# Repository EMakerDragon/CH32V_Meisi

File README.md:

# CH32V_Meisi
これはUIAPduino Pro Micro CH32V003 V1.4をベースに5X7ドットマトリクスLEDを追加した基板名刺です。  
基本的にはUIAPduino Pro Micro CH32V003 V1.4と同じ設計なので同じように使用できます。

Test_program.inoはデフォルトで書き込んでいるプログラムです。  
全点灯,H,E,L,L,O,ランダム点灯 がボタンを押すごとに切り替わります。  
かなり汚いプログラムなので参考にはしないでください。

ベースにしたボード  
UIAPduino Pro Micro CH32V003 V1.4 https://www.uiap.jp/uiapduino/pro-micro/ch32v003/v1dot4

## License
This project is licensed under the Creative Commons Attribution-ShareAlike 4.0 International License.
- [View License Summary](https://creativecommons.org/licenses/by-sa/4.0/deed.ja)
- [View Full Legal Code](https://creativecommons.org/licenses/by-sa/4.0/legalcode)

このプロジェクトは、[YuukiUmeta-UIAP]による「UIAPduino Pro Micro CH32V003 V1.4」をベースにしており、
クリエイティブ・コモンズ 表示 - 継承 4.0 国際 ライセンスの下で提供されています。

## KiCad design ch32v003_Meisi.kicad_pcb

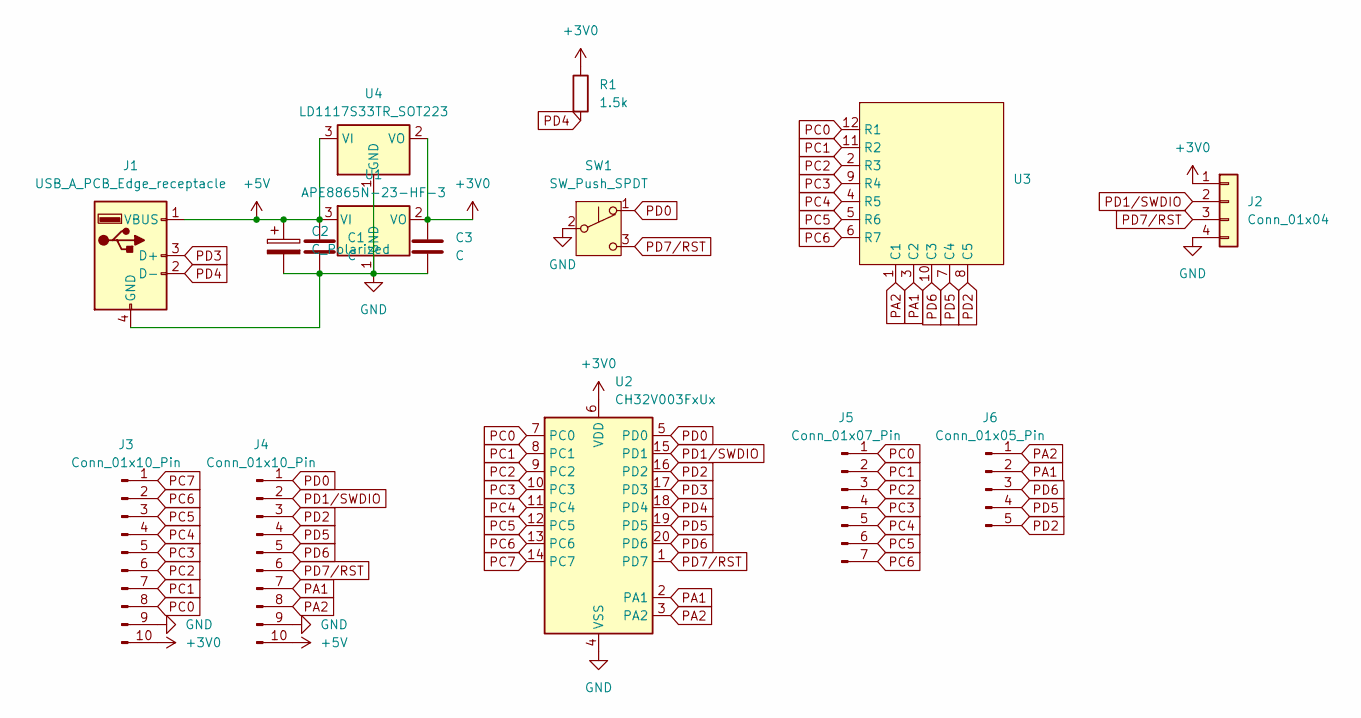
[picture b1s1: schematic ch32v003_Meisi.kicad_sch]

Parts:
C1, C3: C; C_0603_1608Metric
C2: C_Polarized; CP_Radial_D5.0mm_P2.50mm
J1: USB_A_PCB_Edge_receptacle
J2: Conn_01x04; DEBUG_ch32
J3, J4: Conn_01x10_Pin; PinHeader_1x10_P2.54mm_Vertical
J5: Conn_01x07_Pin; PinHeader_1x07_P2.54mm_Vertical
J6: Conn_01x05_Pin; PinHeader_1x05_P2.54mm_Vertical
R1: 1.5k
SW1: SW_Push_SPDT; Push_SW_2Level
U1: APE8865N-23-HF-3; SOT-23
U2: CH32V003FxUx; QFN-20-1EP_3x3mm_P0.4mm_EP1.65x1.65mm
U3: LED_MATRIX
U4: LD1117S33TR_SOT223; SOT-223-3_TabPin2

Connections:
+3V0: C3.1, J2.1, J3.10, R1.1, U1.2 (VO), U2.6 (VDD), U4.2 (VO)
+5V: C1.1, C2.1, J1.1 (VBUS), J4.10, U1.3 (VI), U4.3 (VI)
GND: C1.2, C2.2, C3.2, J1.4 (GND), J2.4, J3.9, J4.9, SW1.2 (B), U1.1 (GND), U2.4 (VSS), U2.21 (VSS), U4.1 (GND)
PA1: J4.7, J6.2, U2.2 (PA1), U3.3 (C2)
PA2: J4.8, J6.1, U2.3 (PA2), U3.1 (C1)
PC0: J3.8, J5.1, U2.7 (PC0), U3.12 (R1)
PC1: J3.7, J5.2, U2.8 (PC1), U3.11 (R2)
PC2: J3.6, J5.3, U2.9 (PC2), U3.2 (R3)
PC3: J3.5, J5.4, U2.10 (PC3), U3.9 (R4)
PC4: J3.4, J5.5, U2.11 (PC4), U3.4 (R5)
PC5: J3.3, J5.6, U2.12 (PC5), U3.5 (R6)
PC6: J3.2, J5.7, U2.13 (PC6), U3.6 (R7)
PC7: J3.1, U2.14 (PC7)
PD0: J4.1, SW1.1 (A), U2.5 (PD0)
PD1/SWDIO: J2.2, J4.2, U2.15 (PD1)
PD2: J4.3, J6.5, U2.16 (PD2), U3.8 (C5)
PD3: J1.3 (D+), U2.17 (PD3)
PD4: J1.2 (D-), R1.2, U2.18 (PD4)
PD5: J4.4, J6.4, U2.19 (PD5), U3.7 (C4)
PD6: J4.5, J6.3, U2.20 (PD6), U3.10 (C3)
PD7/RST: J2.3, J4.6, SW1.3 (C), U2.1 (PD7)

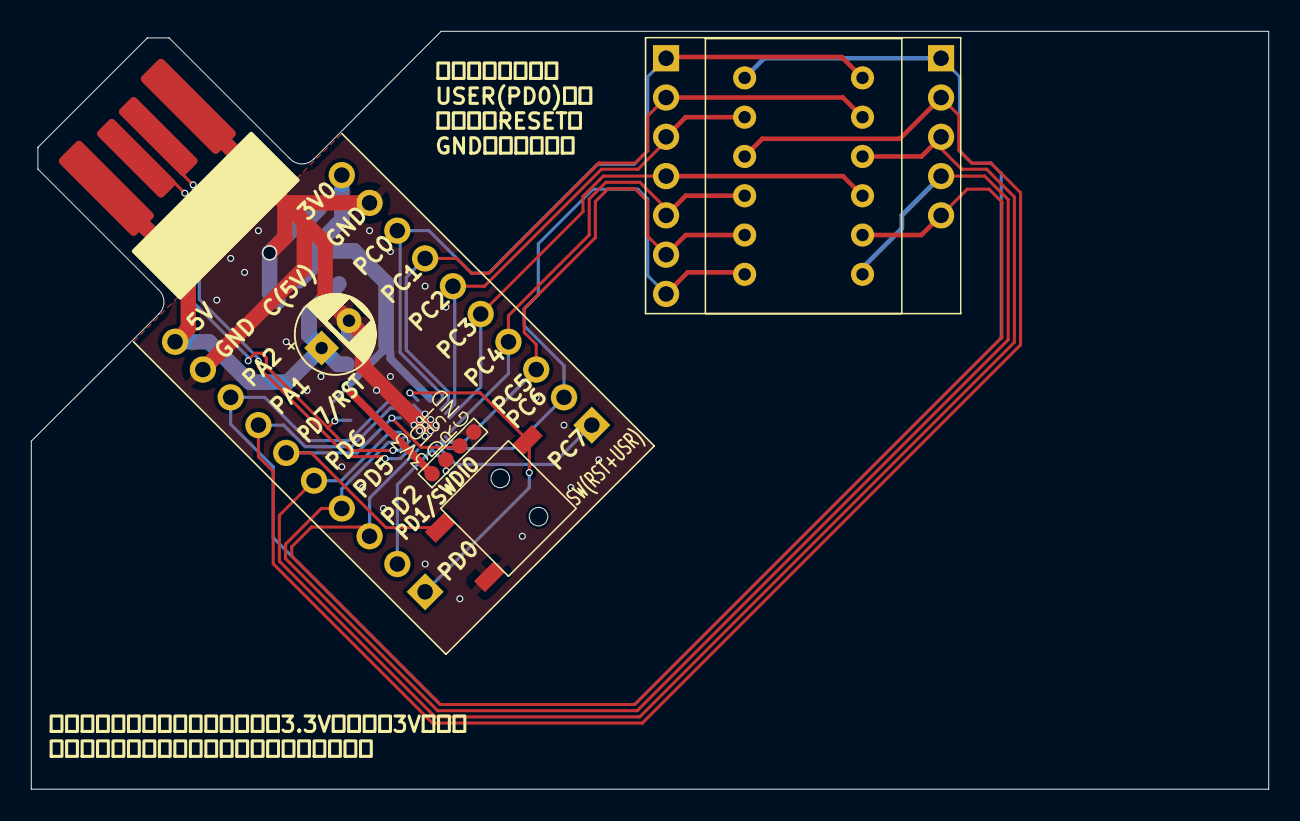
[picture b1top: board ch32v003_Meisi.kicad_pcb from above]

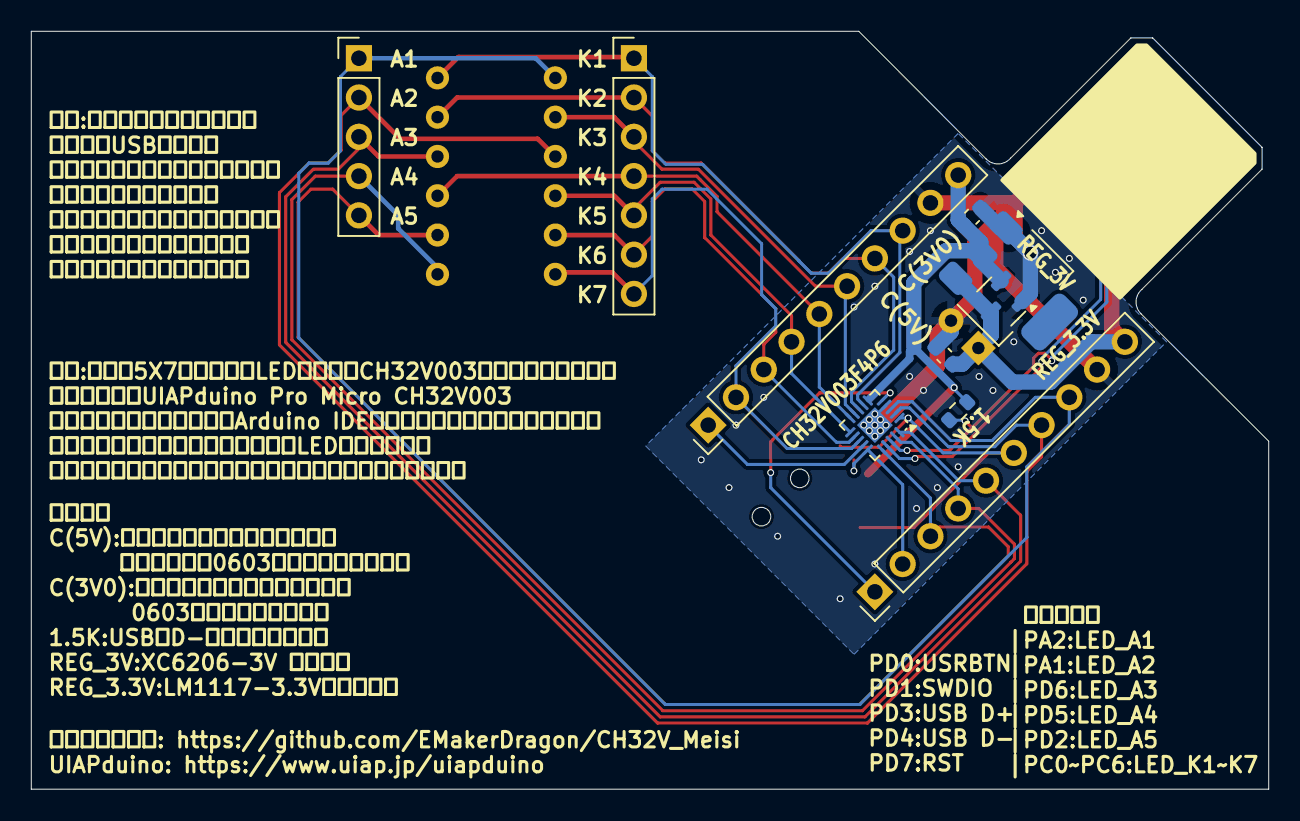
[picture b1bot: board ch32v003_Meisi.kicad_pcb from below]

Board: 2 copper layers, 80.0 x 49.0 mm, 15 parts (10 on the bottom side), 21 nets.
